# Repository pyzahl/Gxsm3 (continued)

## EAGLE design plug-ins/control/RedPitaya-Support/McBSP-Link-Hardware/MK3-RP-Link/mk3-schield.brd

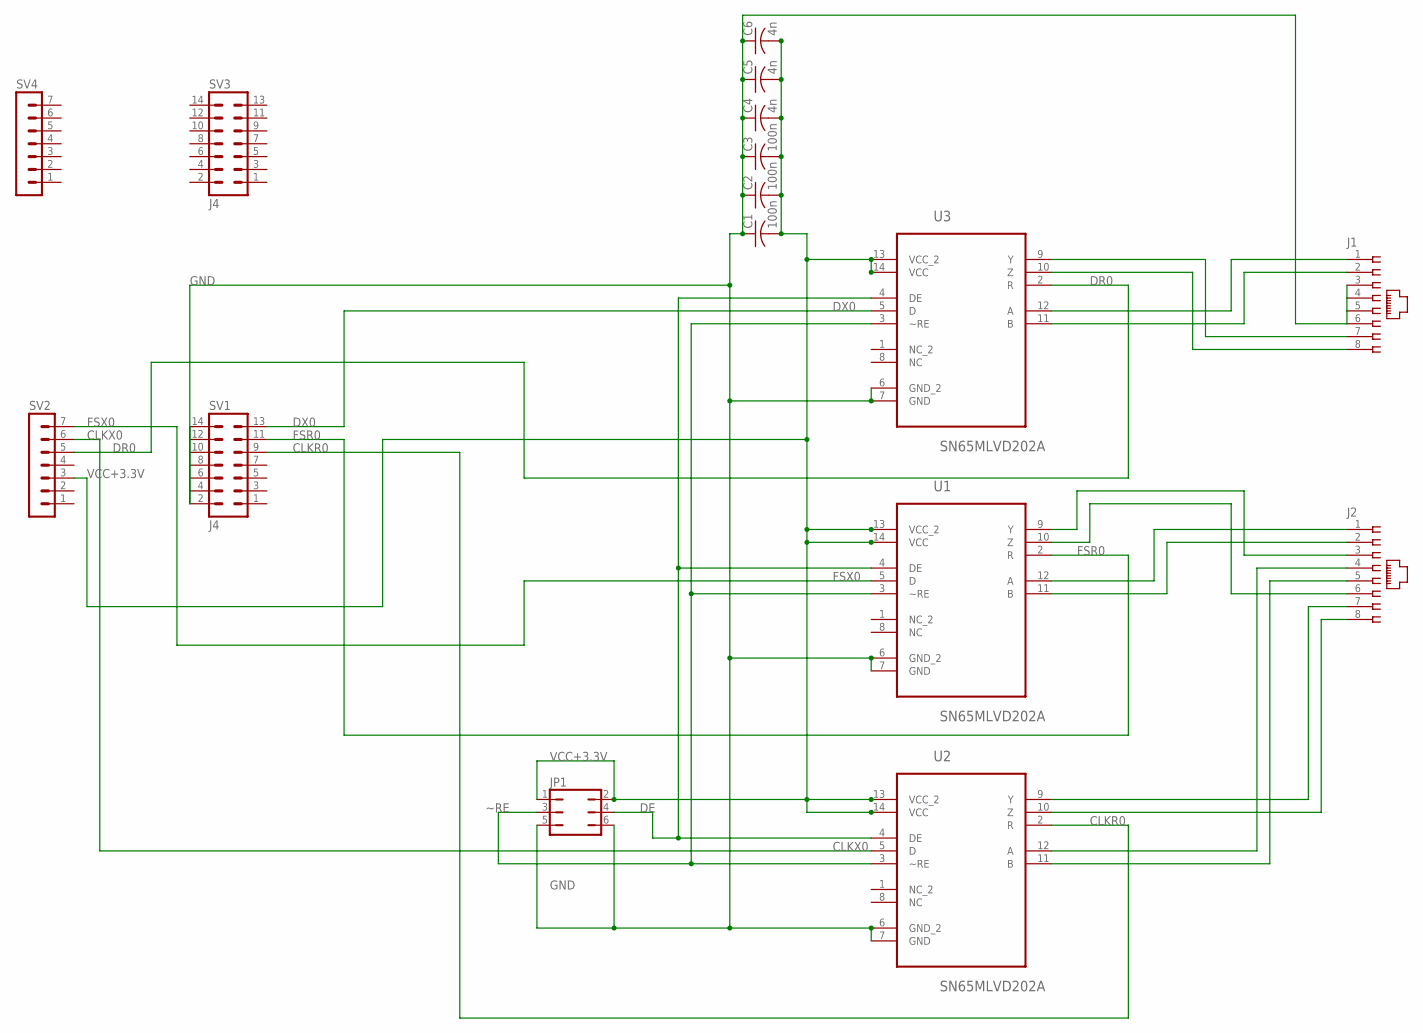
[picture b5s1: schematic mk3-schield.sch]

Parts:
C1, C2, C3: 100n; C0805
C4, C5, C6: 4n; C0805
J1, J2: 557785-1-SHIELD; 557785-1
JP1: JP3Q
SV1, SV3: J4; MA07-2
SV2, SV4: MA07-1
U1, U2, U3: SN65MLVD202A; SOIC127P600X175-14N

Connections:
CLKR0: SV1.9, U2.2 (R)
CLKX0: SV2.6, U2.5 (D)
DE: JP1.4, U1.4 (DE), U2.4 (DE), U3.4 (DE)
DR0: SV2.5, U3.2 (R)
DX0: SV1.13, U3.5 (D)
FSR0: SV1.11, U1.2 (R)
FSX0: SV2.7, U1.5 (D)
GND: C1.1, C2.1, C3.1, C4.1, C5.1, C6.1, J1.3, J1.4, J1.5, J1.6, JP1.5, JP1.6, SV1.2, SV1.4, SV1.6, SV1.8, SV1.10, SV1.12, SV1.14, U1.6 (GND_2), U1.7 (GND), U2.6 (GND_2), U2.7 (GND), U3.6 (GND_2), U3.7 (GND)
unnamed: J1.1, U3.12 (A)
unnamed: J1.2, U3.11 (B)
unnamed: J1.7, U3.9 (Y)
unnamed: J1.8, U3.10 (Z)
unnamed: J2.1, U1.12 (A)
unnamed: J2.2, U1.11 (B)
unnamed: J2.3, U1.9 (Y)
unnamed: J2.6, U1.10 (Z)
unnamed: J2.4, U2.12 (A)
unnamed: J2.5, U2.11 (B)
unnamed: J2.7, U2.9 (Y)
unnamed: J2.8, U2.10 (Z)
VCC+3.3V: C1.2, C2.2, C3.2, C4.2, C5.2, C6.2, JP1.1, JP1.2, SV2.3, U1.13 (VCC_2), U1.14 (VCC), U2.13 (VCC_2), U2.14 (VCC), U3.13 (VCC_2), U3.14 (VCC)
~RE: JP1.3, U1.3 (~RE), U2.3 (~RE), U3.3 (~RE)

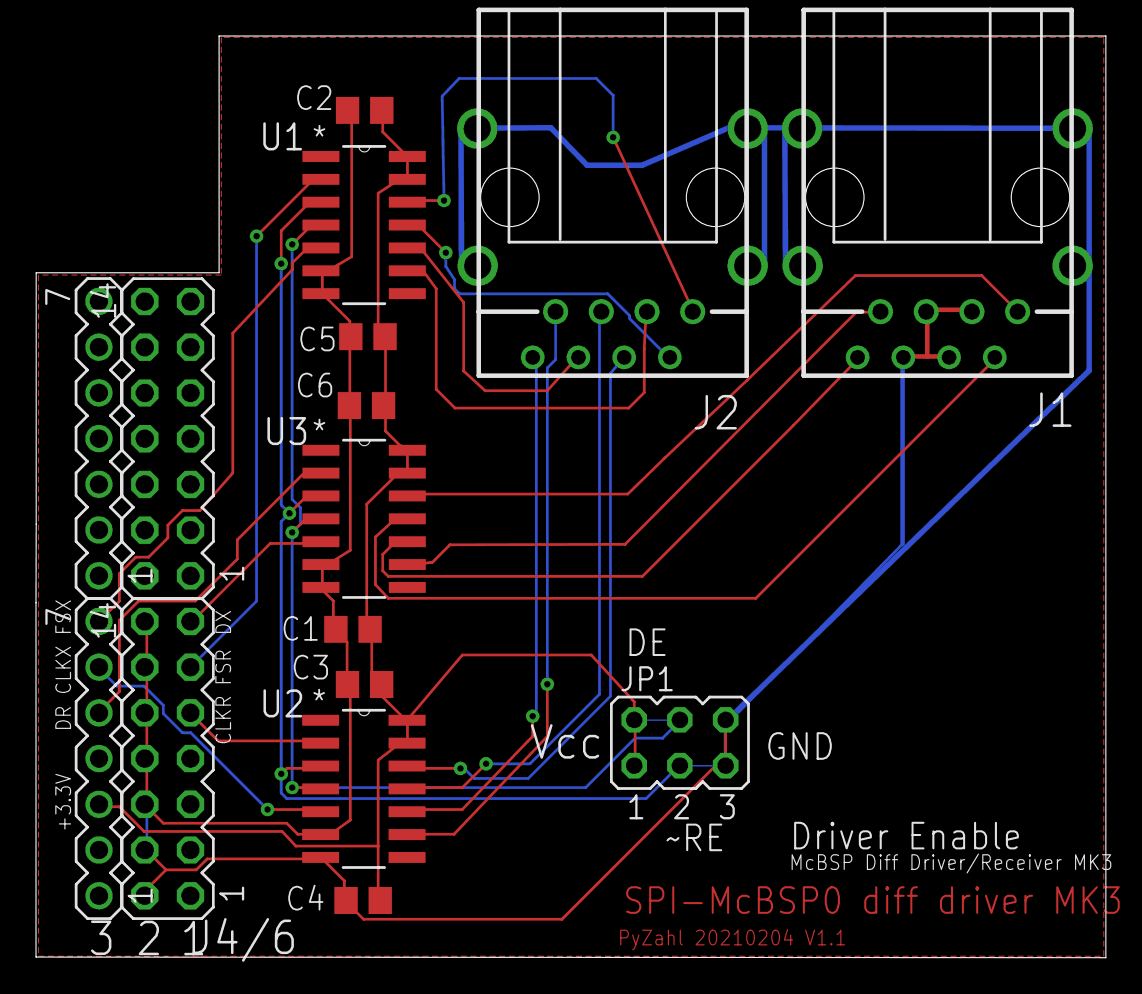
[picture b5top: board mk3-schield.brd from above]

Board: 2 copper layers, 59.4 x 51.2 mm, 16 parts (0 on the bottom side), 22 nets.

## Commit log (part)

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2022-01-12 made gtksourceview optional (not building pyremote)
2022-01-12 log message cleanups scan on/off fixes/cleanups
2022-01-12 added gnome_compile_schmas and install-script
2022-01-12 added experimental flatpak manifest
2022-01-14 testing new simple "icon" based mover "fire" button construct on (Z0+) currently.
2022-01-14 Mover: "Fire Button" new creation from icon with motion/click controllers. Not yet most pretty integration as not "shading". But fully functional. Entry: hooked up new focus controller to catch out-o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
2022-01-15 cleanups and few fixes of plugin lists
2022-01-15 reorganized gxsm application startup procedure
2022-01-16 lots of house keeping...
2022-01-16 view draw update optimizations as of new canvas/image update behavior (whole shot always, no sub region draw, at least not manually defined)
2022-01-16 tuning view refresh
2022-01-20 back ported stages GXSM4 startup and build process to GXSM-3.0. This allows for message dialogs/infos while startup and hardware detection errors message.
2022-01-20 code cleanups, pedantic C++ warning cleanups (enabled now)
2022-01-21 cleanups, schemata: install xml files, fixed default for mx0-curr-gain
2022-01-24 basic flatpak build manifest
2022-01-24 adjusted debug levels
2022-01-24 fixed formatting
2022-01-24 fixed typo
2022-01-25 added about info about all compiled in install paths if debug level set > 1
2022-01-27 lots of DBG message cleanups, DSP MK2/3 auto detection optimize, fall back to HwI base class.
2022-01-30 experimenting with pyremote thread -- not yet completed !!
2022-01-30 porting python emb calls to thread safe g_idle_add join mechanism... in progress
2022-01-30 cleanups
2022-01-31 adjusted includes order
2022-01-31 added gtksourceview git again -- patched on own fork for now
2022-01-31 fixed save as exec cb
2022-01-31 pyremote gxsm sleep now simple usleep
2022-01-31 useconds_t
2022-01-31 fixed missing openCV libs in makefile
2022-01-31 work on waitscan
2022-01-31 issue with thread sleep, trying g_usleep
2022-01-31 experimenting with g_thread vs. gtask/thread
2022-02-02 cleanups. Added warnimg message to python console startup as experimental.
2022-02-14 added mutex to message_list
2022-02-14 testing high priority for scancontrol and view updates g_idle
2022-02-14 adjusting idle priority
2022-02-14 porting thread save py autodisp
2022-02-15 changed push/pop message and idle_add
2022-02-15 testing / tuning scancontrol idle task
2022-02-15 added performance testing/debugging info
2022-02-15 test timing
2022-02-15 optimzing
2022-02-15 performance eval of PCS
2022-02-15 pcs performance testing
2022-02-15 pcs perf...
2022-02-18 backported python remote fully threadded from gxsm4
2022-02-18 added update interval for scan view (spm_scancontrol) to settings. (not exposed to user in gxsm)
2022-02-18 updates on included py scripts
2022-02-21 update comment CVmatch libs
2022-02-22 reveretd setting to not use obsoleted date/time code any more as default
2022-02-28 one more py function patched
2022-02-28 added crop function (testing)
2022-03-01 few patches for pyremote related calls
2022-03-01 patched OpenCV call (lib changes)
2022-03-02 syncing pyremote gxsm3/gxsm4
2022-03-09 fixed idle callback for gxsm.action
2022-03-19 added idle calls
2022-03-19 added missing repeting idle call for movetoxy
2022-03-19 added checked for consistent dsp_scan.xyz_vec reads -- can occurr to interrupt read at rotation computaions -- and 32bit activity is not guranteed to be atomic on DSP level!
2022-03-21 added logging info for movetoxy stages and python command is now blocking until completed
2022-03-21 changed idle move call to timeout
2022-03-22 added tip motion updated
2022-03-22 added tip motion state query option
2022-03-24 updated scan struct mapping
2022-03-24 added graph option to disable scan event adding to MasterScan for VP
2022-03-24 update_scanpos as timeout
2022-03-24 setting scan.start/stop=0 at write_dsp as should never be set here by any means.
2022-03-24 added verify to VP vetor write
2022-03-24 EXPERIMENTAL DSP CODE
2022-03-28 moved signal cache read out of mem init of read thread and before VP start
2022-03-28 reenabled McBSP for probe
2022-04-01 dded query modes for SignalMonitor access: "M" : Mix-IN1, 2, 3 "mNN" : MonitorSignal[NN] -- Monitor Singals at index SigMon[NN]: [Scaled Signal in Unit, raw signal, scale, ret=unit-string] (NN = 00 .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
2022-04-02 fixing PyThread GIL state to not block at exit
2022-04-05 fixed GIL stuff in case of error report situation
2022-04-07 fixed auto filename suggestions
2022-04-07 added object add/remove hooks
2022-04-08 fixed REMOVE-OBJ algorithm
2022-04-08 fixed REMOVE-ALL objects action command
2022-04-14 made RTQ thread safe, can casue issues
2022-04-17 added gxsm python access to manipulate point and rect objects, trigger get point offset and rect coords to setup scan.
2022-04-19 added get data slice fucntion
2022-04-19 removed test code, cleanups
2022-04-20 Create README.md
    copied old plain text README to new README.md
2022-05-08 modified auto detect and corrected load of very old nc files
2022-05-22 Ubuntu 22.04 LTS release
2022-05-24 adjusting dsp_fbs_mx0_current gain from 1.0 to 0.5 as maximum allowed is just 0.5
2022-07-11 Fixed problem with linking of python libs on Ubuntu 22.04
2022-07-11 Fixed problem with linking of python3.10 libs on Ubuntu22.04
2022-07-21 fixing problem with option -h=no in gxsm-gxsm.desktop
2022-07-21 fixed desktop file
    option -h=no is now replaced by -h no
2022-08-31 added new palette schemes
2022-08-31 added new palettes to instal list
2022-09-03 added layer-info copy and lookups (no org transfer yet)
2022-09-05 added copy layerinfo to crop
2022-09-27 added aspect range view mode
2022-09-28 fixed coordinate mappings when in new range aspect mode
2022-09-28 patched more mappings for get coordinat tools
2022-10-12 patched 2nd xp parameter (fast scan more was overriding)
2022-10-25 added experimental RP PACPLL pulse support
2022-10-29 added FFT
2022-11-05 2x6 wh + b01 pulse shaper
2022-11-08 fixed bit packing issue of signed numbers...
2022-12-21 Add build-helper script
2022-12-21 add more options
2022-12-23 planning package target
2022-12-24 Refactored build-bootstrap
2023-01-09 resolved race conditions between points on scan pos update
2023-01-14 updated MK2 DSP feedback delta mixer processing to make fully fucntional in all (new) modes and compatible witgh MK3 behaior
2023-01-30 added auto use of master (Topo in CH0, if available) offset/alpha for createscan function. -- Safety issue when using while scanning as user activate will copy offset to main...!
2023-04-23 Update control_ubuntu22.04
    Adding git as devel dependency
2023-05-08 fixed edge filter to work on full image without selection
2023-06-19 patch of back porting bug on MK2 DSP feedback -- missed set zero of tmp, moved calc to inner case blck to fix efficiently.
2023-06-24 cleanup
2023-07-11 patch to fix crop induced issue w mouse coords
2023-08-24 created global settings parameter set for use w remote control t opass parameters to plugins (math), etc
2023-08-25 patch to view
2023-08-28 added patch to auto disable repeat mode when started from pyremote
2023-08-29 added feature to manipulate/edit LayerInformation
2023-11-22 refactor: untabify and use k&r c-style (tab:8)
    here, we do 2 things:
    - run untabify to remove mistakenly added tabs.
    - re-indent everything with k&r c-style, with c-basic-offset set to 8.
    These are aiming to return this file to the gxsm3 coding standard.
2023-12-14 added MK2 RTquery option to read all ADC's (AIC In 0..7) via gxsm.rtquery('M') 'M' for CH1,2,3, ... 'N' for 4,5,6, 'L' for 0,6,7
2023-12-18 fix / refactor: allow pyremote to stop scripts
    In this CL, we make some significant changes to pyremote.c so that it can
    support *stopping* python scripts during blocking Python calls (e.g.
    time.sleep()). First, we introduce the current architecture and main issue.
    Then, we explain the design changes to fix this issue.
    How pyremote currently works:
    - The main Python interpreter exists in the main thread associated to the
2023-12-27 Revert "Revert "fix / refactor: allow pyremote to stop scripts""
    ... Reverting the revert, i.e. returning to CL that has issues and needs resolving.
    This reverts commit 358491a3b317d403ed97d8ec237c7fc13655fd2a.
2023-12-28 refactor: fit k&r style
    some methods were called like method() instead of method (). Fixing, for
    style purposes.
2023-12-28 [UNTESTED] feat: cause kill with add pending call
    Percy found issues with race conditions using the proposed kill
    mechanism. As mentioned in my original CL, I am not 100% sure why it
    runs. Since it does not seem to function on a secondary device, let's
    try the method I originally proposed: triggering an exception when in
    the main python thread, via Py_AddPendingCall().
2023-12-28 feat: kill python 2 different ways to be sure
    Killing the interpreter with an interrupt via Py_AddPendingCall() does
    not appear to work if we are using gxsm.sleep(). This is because the
    main thread never gets called, because we are never releasing the
    GIL. (I am not sure *why* we do not release the GIL, since the default
    switch interval is not none...). However, this approach *does* work with
    more standard Python calls, where we release the GIL to do I/O work or
2024-02-05 fix: allow python actions+main script to run
    Allow python actions to run simultaneously with the main script, without
    stopping each other. Previously, when one ended it was causing the other
    to end as well!
    After investigation, it was found that this was due to PyDict_Clear(d)
    in destroy_environment(). My best explanation: PyDict_Copy() is a
    shallow, not deep, copy. Since there is some mutable parameter in the
2024-05-10 added Gxsm Python Venv support: Setup a python Venv create using: $ python3 -m venv .gxsm3/pyaction/GxsmPythonVenv so that ~/.gxsm3/pyaction/GxsmPythonVenv exisits and the to be used python is here: 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
    if this is found it will be automatically used.
2024-05-10 added docu
2024-05-28 fixed odd "recursion" issue with PCS limits (neg lim -10 after configm or spin touch/update) configuration dialog. Can't used spinner internal type overload.
2024-06-10 added raw binary IMX178M camera import
2024-06-11 added SER (LUCAM-RECORDER) auto detection to raw16
2024-06-11 work on import auto options/variants SER,...
2024-07-26 patch of MK2 dataprocess mixer feedback source inversion (lin-neg mode MIX0 only effected). Note -- this has NOTHING to do with Z-polarity.
2024-08-23 added/recreated missing file (lost from original working folder as of hard drive failure :( )
2024-10-05 patch for all newer Python versions - works now for all > 3.7 and not limited at 3.10 any more updateted ser_import.C w almost lost work... preparing for PAC-PLL code updates
2024-10-05 updated FPGA logic file
2024-10-09 Add files via upload
    Ubuntu 24.04 port
2024-11-15 added single RP pulse mode option
2024-11-16 work on single pulse shot and RP fast data record to .rpdata file storage plus python data access
2024-11-16 FPGA update for single pulse mode
2024-12-19 push, udpate
2025-01-08 backported profile unit/label/tile on-the-fly update
2025-03-10 backporting in progress: remote action check/uncheck hooks
2025-06-09 backport of pyremote probe data query
2025-09-06 backported OSD position patch
2025-12-08 restructuring files
    * removed nctopng from debian package
    * removed gxsm-nc-thumbnailer from package
    * files are now part of the gxsm4 repository and part of the gxsm-nc-thumbnailer package
2025-12-08 Added missing dependency to json-glib
2026-04-27 Fixing python3.7 dependency
